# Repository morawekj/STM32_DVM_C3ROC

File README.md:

# STM32_DVM_C3ROC

This is a fork of the STM32 DVM V4 from Scott Zimmerman N3XCC / Repeater Builder
Inspired from a similar design: github.com/wojciechk8/MMDVM_pog
Low-pass filter design by SQ6POG

I design a new KiCad Design with some improvements and separate LED Board with I2C and RS232 Display connections. Also with an 5V 3.5A DC/DC converter with TI TPS54360(B) for the Raspberry PI, so that can powered from the radios DC voltage. Also add some ferrite beads and USBCL6 TVS protection. Connection to the LED/Display is a 20 Pin ribbon cable.

This project is mainly design for use for use on Chaos Computer Clubs Radio Teams (c3roc) DMR repeaters. All credits go to first designers. May be some others HAMs find this useful and feel free to use.

PCB and Components can be easy source by some prototype manufactures.

Enjoy RFguy DG3FDM

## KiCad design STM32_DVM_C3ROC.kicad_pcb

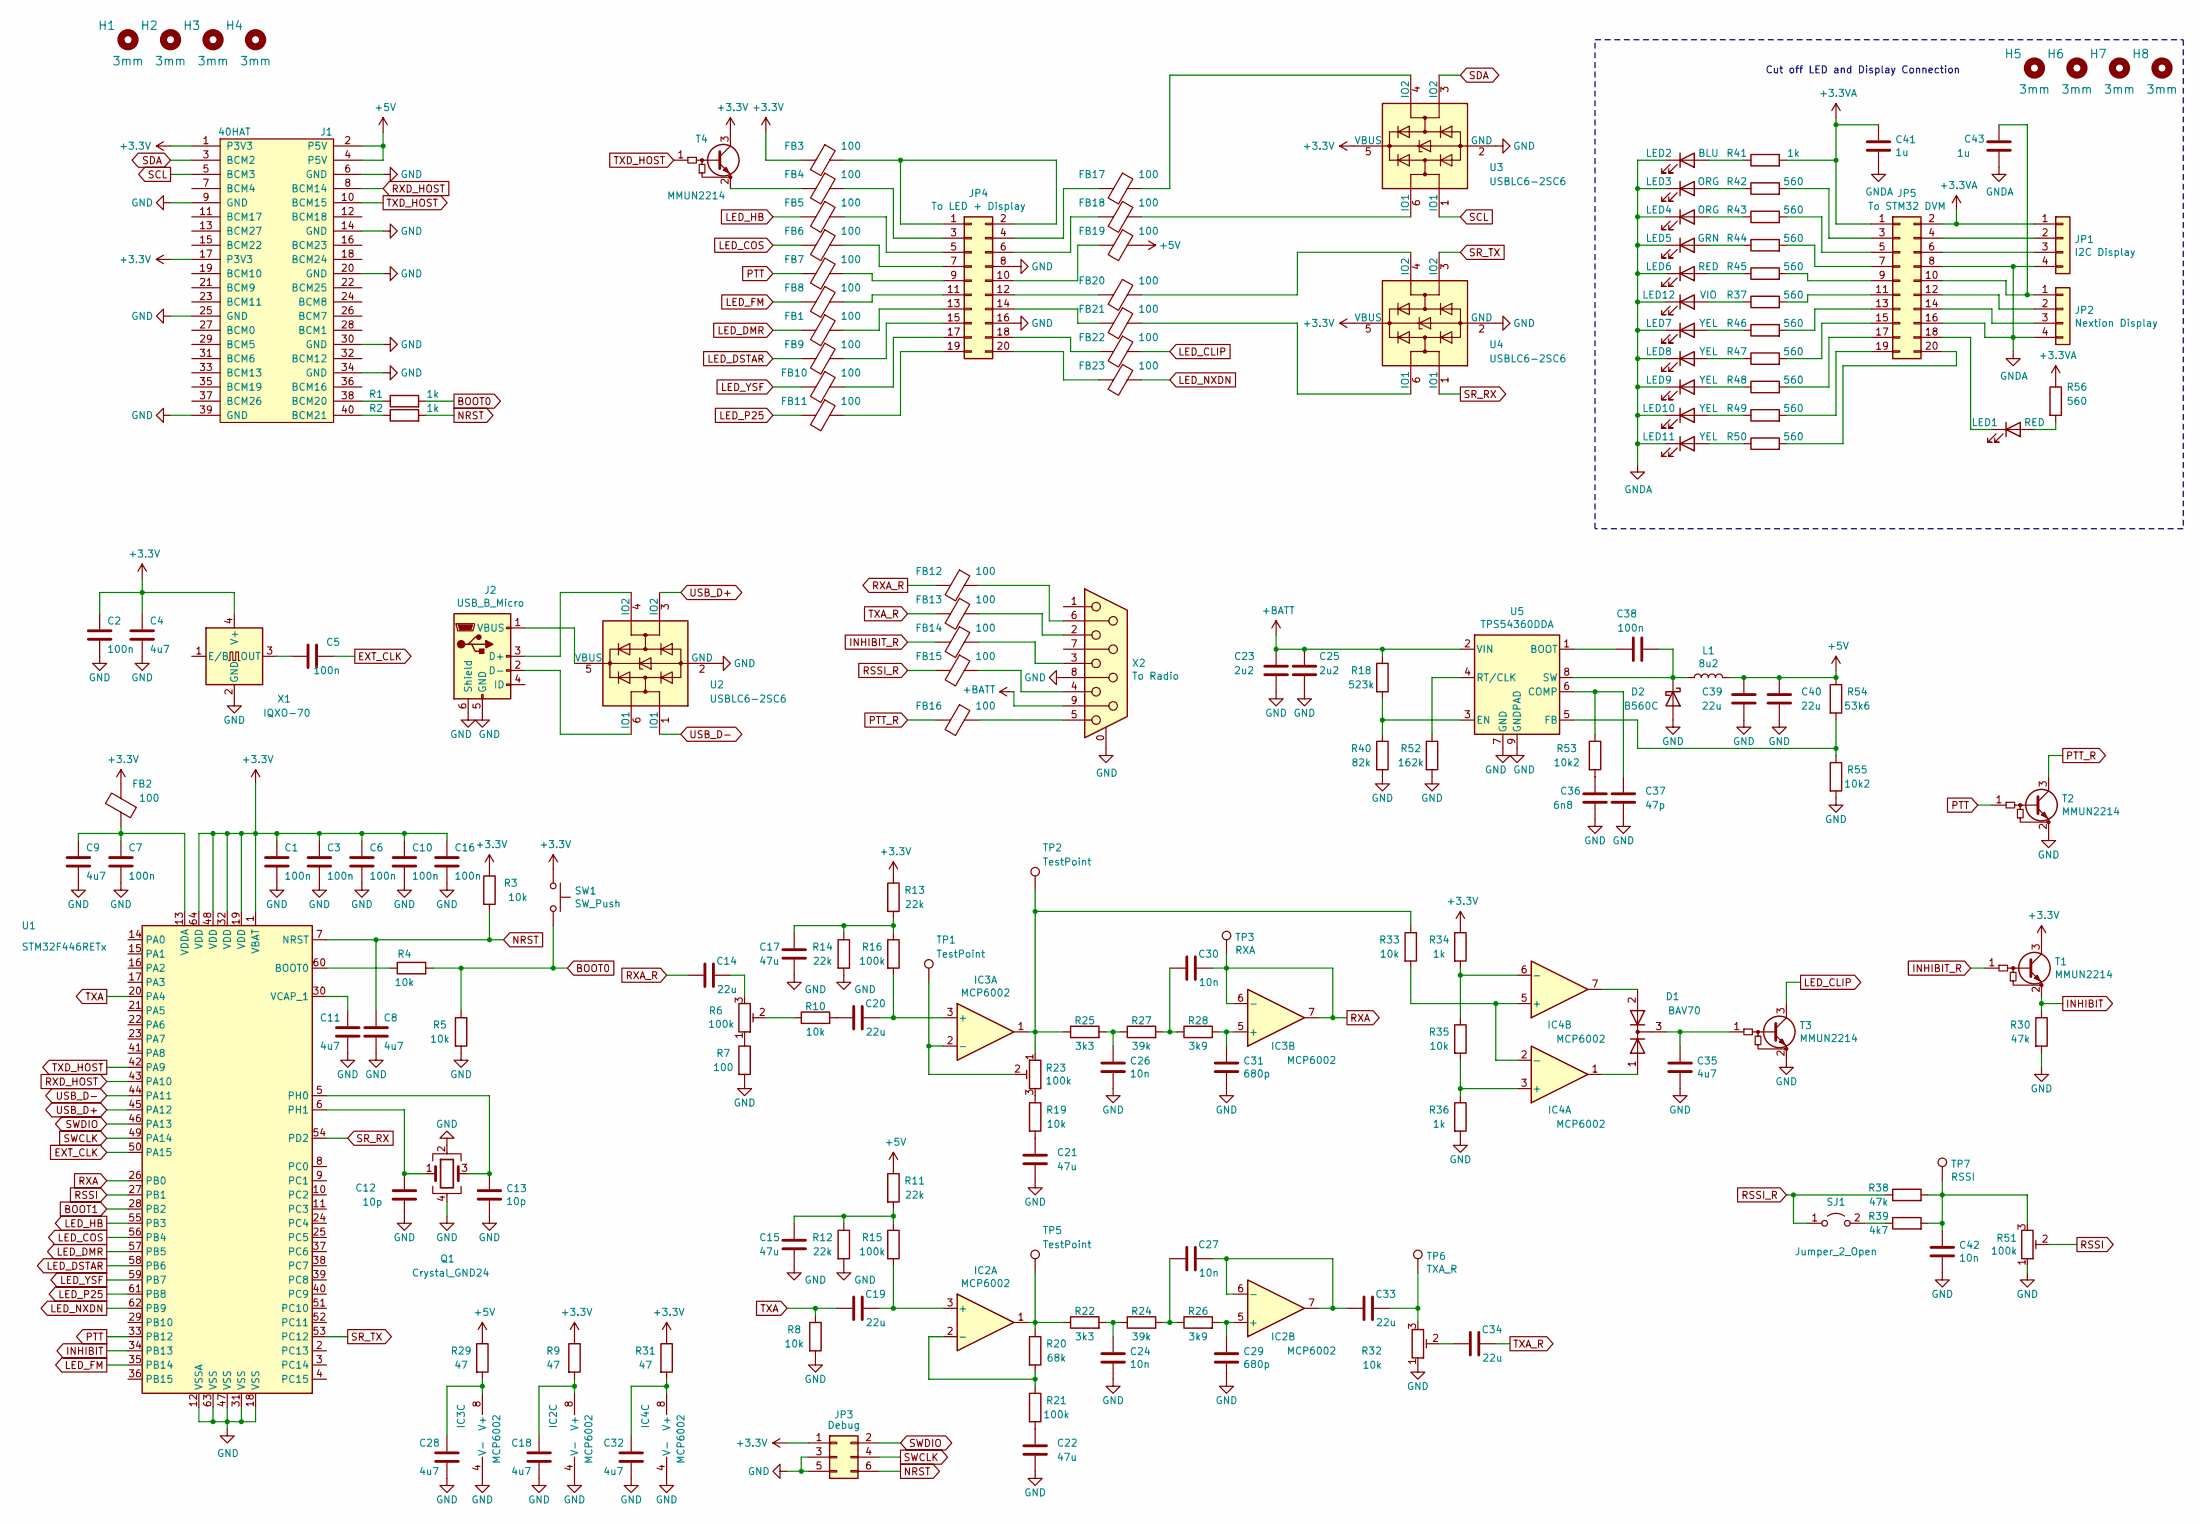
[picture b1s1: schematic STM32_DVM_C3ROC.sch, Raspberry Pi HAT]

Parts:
C1, C2, C3, C5, C6, C7, C10, C16, C38: 100n; C_0603_1608Metric
C4, C8, C9, C11, C18, C28, C32, C35: 4u7; C_1206_3216Metric
C12, C13: 10p; C_0603_1608Metric
C14, C19, C20, C33, C34, C39, C40: 22u; C_1210_3225Metric
C15, C17, C21, C22: 47u; C_1210_3225Metric
C23, C25: 2u2; C_1206_3216Metric
C24, C26, C27, C30, C42: 10n; C_0603_1608Metric
C29, C31: 680p; C_0603_1608Metric
C36: 6n8; C_0603_1608Metric
C37: 47p; C_0603_1608Metric
C41, C43: 1u; C_1206_3216Metric
D1: BAV70; SOT-23
D2: B560C; D_SMC
FB1, FB2, FB3, FB4, FB5, FB6, FB7, FB8, FB9, FB10, FB11, FB12, FB13, FB14, FB15, FB16, FB17, FB18, FB19, FB20, FB21, FB22, FB23: 100; L_0603_1608Metric
H1, H2, H3, H4, H5, H6, H7, H8: 3mm; NPTH_3mm_ID
IC2, IC3, IC4: MCP6002; SO-8_3.9x4.9mm_P1.27mm
J1: 40HAT; PinSocket_2x20_P2.54mm_Vertical
J2: USB_B_Micro; USB_Micro-B_Molex_47346-0001
JP1: I2C Display; PinHeader_1x04_P2.54mm_Vertical
JP2: Nextion Display; PinHeader_1x04_P2.54mm_Vertical
JP3: Debug; PinHeader_2x03_P2.54mm_Vertical
JP4: To LED + Display; PinHeader_2x10_P2.54mm_Vertical
JP5: To STM32 DVM; PinHeader_2x10_P2.54mm_Vertical
L1: 8u2; L_Bourns_SRP7028A_7.3x6.6mm
LED1, LED6: RED; LED_0603_1608Metric
LED2: BLU; LED_0603_1608Metric
LED3, LED4: ORG; LED_0603_1608Metric
LED5: GRN; LED_0603_1608Metric
LED7, LED8, LED9, LED10, LED11: YEL; LED_0603_1608Metric
LED12: VIO; LED_0603_1608Metric
Q1: Crystal_GND24; Crystal_SMD_3225-4Pin_3.2x2.5mm
R1, R2, R34, R36, R41: 1k; R_0603_1608Metric
R3, R4, R5, R8, R10, R19, R33, R35: 10k; R_0603_1608Metric
R6, R23, R51: 100k; Potentiometer_Bourns_3296W_Vertical
R7: 100; R_0603_1608Metric
R9, R29, R31: 47; R_0603_1608Metric
R11, R12, R13, R14: 22k; R_0603_1608Metric
R15, R16, R21: 100k; R_0603_1608Metric
R18: 523k; R_0603_1608Metric
R20: 68k; R_0603_1608Metric
R22, R25: 3k3; R_0603_1608Metric
R24, R27: 39k; R_0603_1608Metric
R26, R28: 3k9; R_0603_1608Metric
R30, R38: 47k; R_0603_1608Metric
R32: 10k; Potentiometer_Bourns_3296W_Vertical
R37, R42, R43, R44, R45, R46, R47, R48, R49, R50, R56: 560; R_0603_1608Metric
R39: 4k7; R_0603_1608Metric
R40: 82k; R_0603_1608Metric
R52: 162k; R_0603_1608Metric
R53, R55: 10k2; R_0603_1608Metric
R54: 53k6; R_0603_1608Metric
SJ1: Jumper_2_Open; SolderJumper-2_P1.3mm_Open_Pad1.0x1.5mm
SW1: SW_Push; SW_SPST_SKQG_WithoutStem
T1, T2, T3, T4: MMUN2214; SOT-23
TP1, TP2, TP5: TestPoint; TestPoint_Pad_D1.5mm
TP3: RXA; TestPoint_Pad_D1.5mm
TP6: TXA_R; TestPoint_Pad_D1.5mm
TP7: RSSI; TestPoint_Pad_D1.5mm
U1: STM32F446RETx; LQFP-64_10x10mm_P0.5mm
U2, U3, U4: USBLC6-2SC6; SOT-23-6
U5: TPS54360DDA; TI_SO-PowerPAD-8_ThermalVias
X1: IQXO-70; Oscillator_SMD_IQD_IQXO70-4Pin_7.5x5.0mm
X2: To Radio; DSUB-9_Female_Horizontal_P2.77x2.84mm_EdgePinOffset4.94mm_H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

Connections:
+3.3VA: C41.1, JP1.1, JP5.1, JP5.2, R41.2, R56.1
+3V3: C1.1, C2.1, C3.1, C4.1, C6.1, C10.1, C16.1, FB2.2, FB3.2, J1.1 (P3V3), J1.17 (P3V3), JP3.1, R3.1, R9.1, R13.1, R31.1, R34.1, SW1.1, T1.3 (C), T4.3 (C), U1.1 (VBAT), U1.19 (VDD), U1.32 (VDD), U1.48 (VDD), U1.64 (VDD), U3.5 (VBUS), U4.5 (VBUS), X1.4 (V+)
+5V: C39.1, C40.1, FB19.1, J1.2 (P5V), J1.4 (P5V), L1.2, R11.1, R29.1, R54.1
+BATT: C23.1, C25.1, R18.1, U5.2 (VIN), X2.9
BOOT0: R1.2, R4.2, R5.1, SW1.2
EXT_CLK: C5.2, U1.50 (PA15)
GND: C1.2, C2.2, C3.2, C4.2, C6.2, C7.2, C8.2, C9.2, C10.2, C11.2, C12.2, C13.2, C15.2, C16.2, C17.2, C18.2, C21.2, C22.2, C23.2, C24.2, C25.2, C26.2, C28.2, C29.2, C31.2, C32.2, C35.2, C36.2, C37.2, C39.2, C40.2, C42.2, D2.2 (A), IC2.4 (V-), IC3.4 (V-), IC4.4 (V-), J1.6 (GND), J1.9 (GND), J1.14 (GND), J1.20 (GND), J1.25 (GND), J1.30 (GND), J1.34 (GND), J1.39 (GND), J2.5 (GND), J2.6 (Shield), JP3.3, JP3.5, JP4.8, JP4.16, Q1.2, Q1.4, R5.2, R7.2, R8.2, R12.2, R14.2, R30.2, R32.1, R36.2, R40.2, R51.1, R52.2, R55.2, T2.2 (E), T3.2 (E), U1.12 (VSSA), U1.18 (VSS), U1.31 (VSS), U1.47 (VSS), U1.63 (VSS), U2.2 (GND), U3.2 (GND), U4.2 (GND), U5.7 (GND), U5.9 (GNDPAD), X1.2 (GND), X2.0 (PAD), X2.8
GNDA: C41.2, C43.2, JP1.4, JP2.4, JP5.8, JP5.16, LED2.1 (K), LED3.1 (K), LED4.1 (K), LED5.1 (K), LED6.1 (K), LED7.1 (K), LED8.1 (K), LED9.1 (K), LED10.1 (K), LED11.1 (K), LED12.1 (K)
INHIBIT: R30.1, T1.2 (E), U1.34 (PB13)
INHIBIT_R: FB14.2, T1.1 (B)
LED_CLIP: FB22.1, T3.3 (C)
LED_COS: FB6.2, U1.56 (PB4)
LED_DMR: FB1.2, U1.57 (PB5)
LED_DSTAR: FB9.2, U1.58 (PB6)
LED_FM: FB8.2, U1.35 (PB14)
LED_HB: FB5.2, U1.55 (PB3)
LED_NXDN: FB23.1, U1.62 (PB9)
LED_P25: FB11.2, U1.61 (PB8)
LED_YSF: FB10.2, U1.59 (PB7)
NRST: C8.1, JP3.6, R2.2, R3.2, U1.7 (NRST)
unnamed: C5.1, X1.3 (OUT)
unnamed: C7.1, C9.1, FB2.1, U1.13 (VDDA)
unnamed: C11.1, U1.30 (VCAP_1)
unnamed: C12.1, Q1.1, U1.6 (PH1)
unnamed: C13.1, Q1.3, U1.5 (PH0)
unnamed: C14.2, R6.3
unnamed: C15.1, R11.2, R12.1, R15.1
unnamed: C17.1, R13.2, R14.1, R16.1
unnamed: C18.1, IC2.8 (V+), R9.2
unnamed: C19.2, IC2.3 (+), R15.2
unnamed: C20.1, R10.2
unnamed: C20.2, IC3.3 (+), R16.2
unnamed: C21.1, R19.2
unnamed: C22.1, R21.2
unnamed: C24.1, R22.2, R24.1
unnamed: C26.1, R25.2, R27.1
unnamed: C27.1, R24.2, R26.1
unnamed: C27.2, C33.1, IC2.6 (-), IC2.7
unnamed: C28.1, IC3.8 (V+), R29.2
unnamed: C29.1, IC2.5 (+), R26.2
unnamed: C30.1, R27.2, R28.1
unnamed: C31.1, IC3.5 (+), R28.2
unnamed: C32.1, IC4.8 (V+), R31.2
unnamed: C33.2, R32.3, TP6.1
unnamed: C34.1, R32.2
unnamed: C35.1, D1.3 (K), T3.1 (B)
unnamed: C36.1, R53.2
unnamed: C37.1, R53.1, U5.6 (COMP)
unnamed: C38.1, U5.1 (BOOT)
unnamed: C38.2, D2.1 (K), L1.1, U5.8 (SW)
unnamed: C42.1, R38.2, R39.2, R51.3, TP7.1
unnamed: C43.1, JP2.1, JP5.10
unnamed: D1.1 (A), IC4.1
unnamed: D1.2 (A), IC4.7
unnamed: FB1.1, JP4.13
unnamed: FB3.1, JP4.1, JP4.2
unnamed: FB4.1, JP4.3
unnamed: FB4.2, T4.2 (E)
unnamed: FB5.1, JP4.5
unnamed: FB6.1, JP4.7
unnamed: FB7.1, JP4.9
unnamed: FB8.1, JP4.11
unnamed: FB9.1, JP4.15
unnamed: FB10.1, JP4.17
unnamed: FB11.1, JP4.19
unnamed: FB12.1, X2.6
unnamed: FB13.1, X2.2
unnamed: FB14.1, X2.3
unnamed: FB15.1, X2.4
unnamed: FB16.1, X2.5
unnamed: FB17.1, U3.4 (IO2)
unnamed: FB17.2, JP4.4
unnamed: FB18.1, U3.6 (IO1)
unnamed: FB18.2, JP4.6
unnamed: FB19.2, JP4.10
unnamed: FB20.1, U4.4 (IO2)
unnamed: FB20.2, JP4.12
unnamed: FB21.1, U4.6 (IO1)
unnamed: FB21.2, JP4.14
unnamed: FB22.2, JP4.18
unnamed: FB23.2, JP4.20
unnamed: IC2.1, R20.1, R22.1, TP5.1
unnamed: IC2.2 (-), R20.2, R21.1
unnamed: IC3.1, R23.1, R25.1, R33.1, TP2.1
unnamed: IC3.2 (-), R23.2, TP1.1
unnamed: IC4.2 (-), IC4.5 (+), R33.2
unnamed: IC4.3 (+), R35.2, R36.1
unnamed: IC4.6 (-), R34.2, R35.1
unnamed: J1.38 (BCM20), R1.1
unnamed: J1.40 (BCM21), R2.1
unnamed: J2.1 (VBUS), U2.5 (VBUS)
unnamed: J2.2 (D-), U2.6 (IO1)
unnamed: J2.3 (D+), U2.4 (IO2)
unnamed: JP1.2, JP5.4
unnamed: JP1.3, JP5.6
unnamed: JP2.2, JP5.12
unnamed: JP2.3, JP5.14
unnamed: JP5.3, R42.2
unnamed: JP5.5, R43.2
unnamed: JP5.7, R44.2
unnamed: JP5.9, R45.2
unnamed: JP5.11, R37.2
unnamed: JP5.13, R46.2
unnamed: JP5.15, R47.2
unnamed: JP5.17, R48.2
unnamed: JP5.18, LED1.1 (K)
unnamed: JP5.19, R49.2
unnamed: JP5.20, R50.2
unnamed: LED1.2 (A), R56.2
unnamed: LED2.2 (A), R41.1
unnamed: LED3.2 (A), R42.1
unnamed: LED4.2 (A), R43.1
unnamed: LED5.2 (A), R44.1
unnamed: LED6.2 (A), R45.1
unnamed: LED7.2 (A), R46.1
unnamed: LED8.2 (A), R47.1
unnamed: LED9.2 (A), R48.1
unnamed: LED10.2 (A), R49.1
unnamed: LED11.2 (A), R50.1
unnamed: LED12.2 (A), R37.1
unnamed: R4.1, U1.60 (BOOT0)
unnamed: R6.1, R7.1
unnamed: R6.2, R10.1
unnamed: R18.2, R40.1, U5.3 (EN)
unnamed: R19.1, R23.3
unnamed: R39.1, SJ1.2 (B)
unnamed: R52.1, U5.4 (RT/CLK)
unnamed: R54.2, R55.1, U5.5 (FB)
PTT: FB7.2, T2.1 (B), U1.33 (PB12)
PTT_R: FB16.2, T2.3 (C)
RSSI: R51.2, U1.27 (PB1)
RSSI_R: FB15.2, R38.1, SJ1.1 (A)
RXA: C30.2, IC3.6 (-), IC3.7, TP3.1, U1.26 (PB0)
RXA_R: C14.1, FB12.2
RXD_HOST: J1.8 (BCM14), U1.43 (PA10)
SCL: J1.5 (BCM3), U3.1 (IO1)
SDA: J1.3 (BCM2), U3.3 (IO2)
SR_RX: U1.54 (PD2), U4.1 (IO1)
SR_TX: U1.53 (PC12), U4.3 (IO2)
SWCLK: JP3.4, U1.49 (PA14)
SWDIO: JP3.2, U1.46 (PA13)
TXA: C19.1, R8.1, U1.20 (PA4)
TXA_R: C34.2, FB13.2
TXD_HOST: J1.10 (BCM15), T4.1 (B), U1.42 (PA9)
USB_D+: U1.45 (PA12), U2.3 (IO2)
USB_D-: U1.44 (PA11), U2.1 (IO1)

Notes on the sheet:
Cut off LED and Display Connection

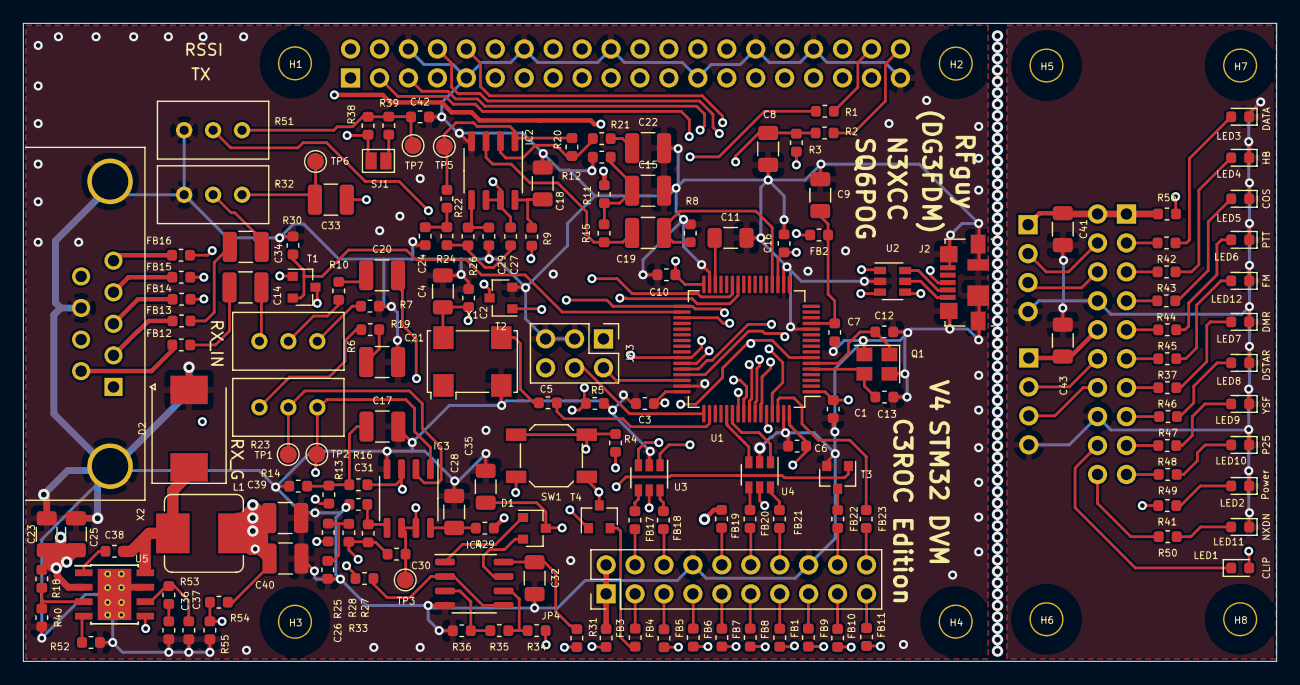
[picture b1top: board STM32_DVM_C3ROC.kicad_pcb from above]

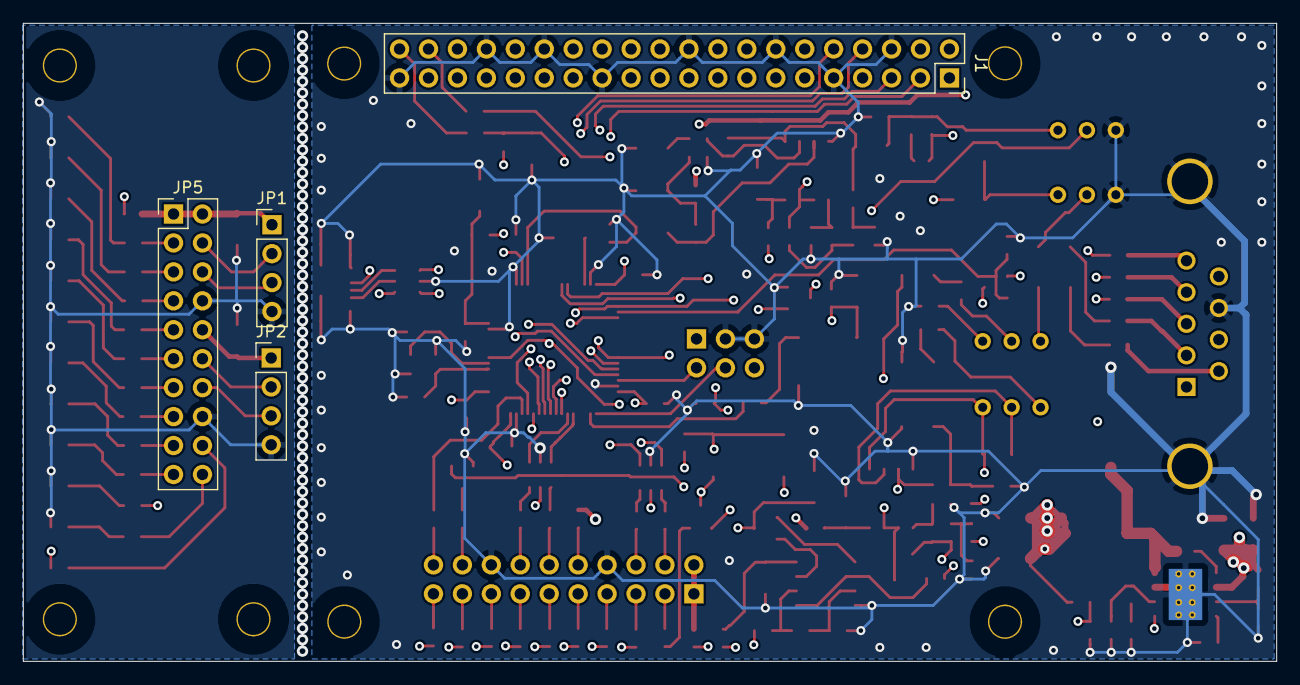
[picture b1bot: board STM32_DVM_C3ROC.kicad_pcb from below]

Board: 4 copper layers, 110.0 x 56.0 mm, 174 parts (4 on the bottom side), 146 nets.

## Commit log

2020-11-17 KiCad Project mit Pi Hat Template angelegt
2020-11-17 initail commit
2020-11-17 Beginn Schaltplan
2020-11-18 Schaltplan bis auf USB und DC/DC komplett
2020-11-18 Schaltplan fertig, Footprints zugewiesen, PCB Beginn platzierung
2020-11-18 Zwei Fehler im Schaltplan gefixt
2020-11-19 Etwas Bauteil Schubsen
2020-11-19 Platzierung 90 % komplett
2020-11-19 LCSC Part List angelegt, Footprints angepasst
2020-11-22 Layout 80 %, kleine Korrekturen
2020-11-23 Layout fertig für review
2020-11-25 Layout fertig, Produktionsdaten für JCLPCB erzeugt
2020-11-26 Produktionsdaten für JCLPCB korrigiert
2020-11-27 Read me angepasst
2022-04-09 no message
